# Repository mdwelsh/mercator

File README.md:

# Mercator

Mercator is a spherical persistence-of-vision display based on ESP32 and
DotStar LEDs. This repo contains the full source files, laser cut and 3D
printed parts designs, and custom PCB design.

For more details, please check out the article here:
https://mdwdotla.medium.com/mercator-an-esp32-based-spherical-persistence-of-vision-display-a4beff4f826e

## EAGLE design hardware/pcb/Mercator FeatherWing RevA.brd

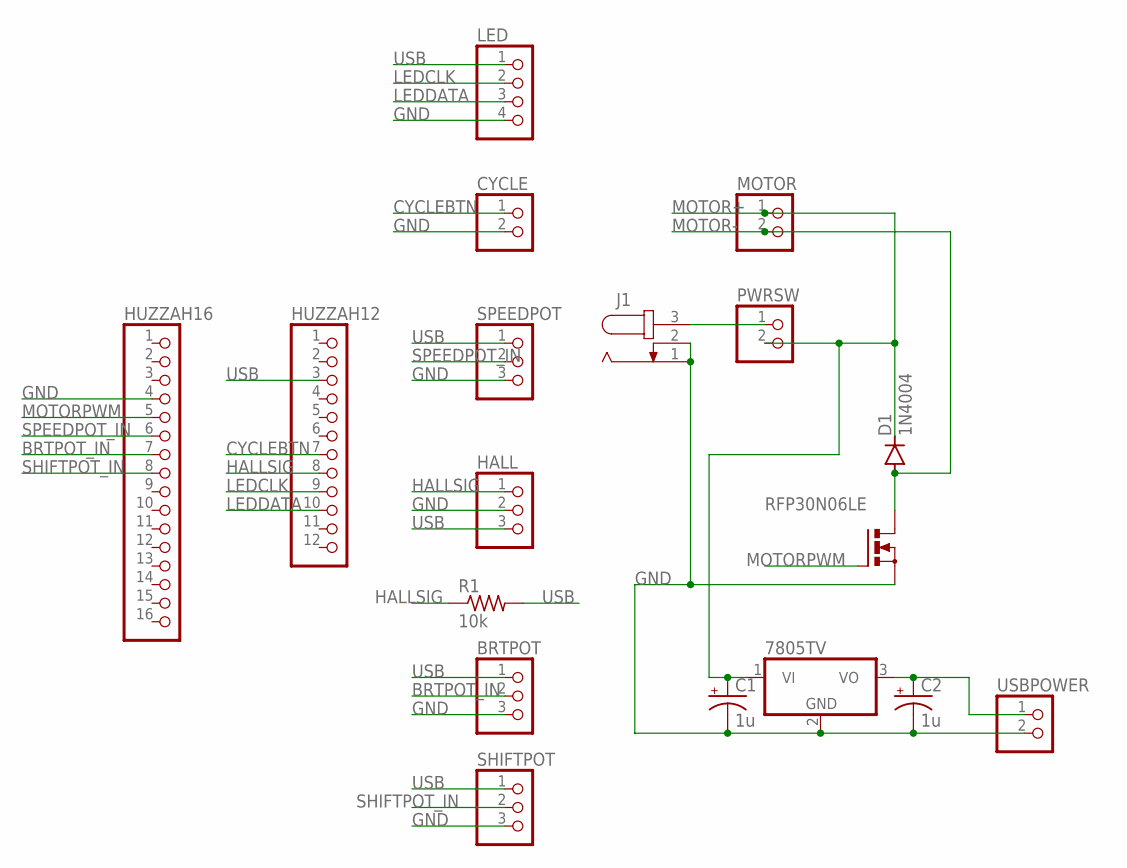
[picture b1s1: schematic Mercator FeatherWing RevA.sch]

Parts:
7805ABV: 7805TV; TO220V
BRTPOT: PINHD-1X3; 1X03
C1, C2: 1u; E2-5
CYCLE: PINHD-1X2; 1X02
D1: 1N4004; DO41-10
HALL: PINHD-1X3; 1X03
HUZZAH12: PINHD-1X12; 1X12
HUZZAH16: PINHD-1X16; 1X16
J1: JACK-PLUG0; SPC4077
LED: PINHD-1X4; 1X04
MOTOR: PINHD-1X2; 1X02
PWRSW: PINHD-1X2; 1X02
R1: 10k; 0207/10
RFP30N06LE: PMOSFET_NTO220BV; TO220BV
SHIFTPOT: PINHD-1X3; 1X03
SPEEDPOT: PINHD-1X3; 1X03
USBPOWER: PINHD-1X2; 1X02

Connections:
BRTPOT_IN: BRTPOT.2, HUZZAH16.7
CYCLEBTN: CYCLE.1, HUZZAH12.7
GND: 7805ABV.2 (GND), BRTPOT.3, C1.-, C2.-, CYCLE.2, HALL.2, HUZZAH16.4, J1.1, J1.2, LED.4, RFP30N06LE.S, SHIFTPOT.3, SPEEDPOT.3, USBPOWER.2
HALLSIG: HALL.1, HUZZAH12.8, R1.1
LEDCLK: HUZZAH12.9, LED.2
LEDDATA: HUZZAH12.10, LED.3
MOTOR+: 7805ABV.1 (VI), C1.+, D1.C, MOTOR.1, PWRSW.2
MOTOR-: D1.A, MOTOR.2, RFP30N06LE.D
MOTORPWM: HUZZAH16.5, RFP30N06LE.G
unnamed: J1.3, PWRSW.1
SHIFTPOT_IN: HUZZAH16.8, SHIFTPOT.2
SPEEDPOT_IN: HUZZAH16.6, SPEEDPOT.2
USB: BRTPOT.1, HALL.3, HUZZAH12.3, LED.1, R1.2, SHIFTPOT.1, SPEEDPOT.1
USB+: 7805ABV.3 (VO), C2.+, USBPOWER.1

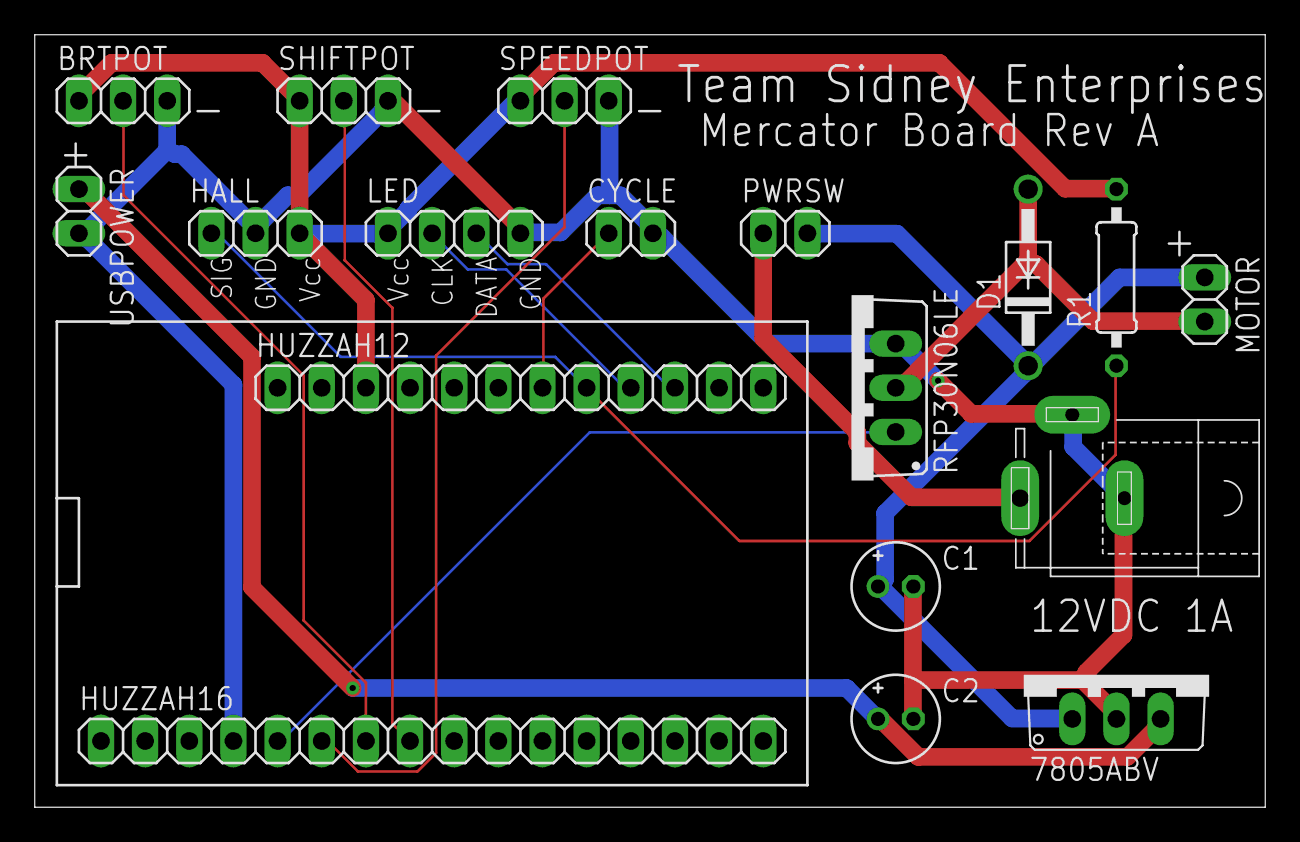
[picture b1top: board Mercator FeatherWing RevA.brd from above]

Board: 2 copper layers, 70.8 x 44.4 mm, 18 parts (0 on the bottom side), 14 nets.

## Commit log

2020-11-29 Migrating files from old repo
2020-11-29 Fix hollowknight name
2020-11-29 Fix README
2020-11-29 Add .gitignore
2020-11-29 Cleanup
2020-11-29 Adding hardware design files.
2020-11-29 Fix filename
2020-11-29 Rename
2020-11-29 Cleanups.
2020-11-29 Adding more README content
2020-11-29 Fix image
2020-11-29 Fix markdown
2020-11-29 Fix link
